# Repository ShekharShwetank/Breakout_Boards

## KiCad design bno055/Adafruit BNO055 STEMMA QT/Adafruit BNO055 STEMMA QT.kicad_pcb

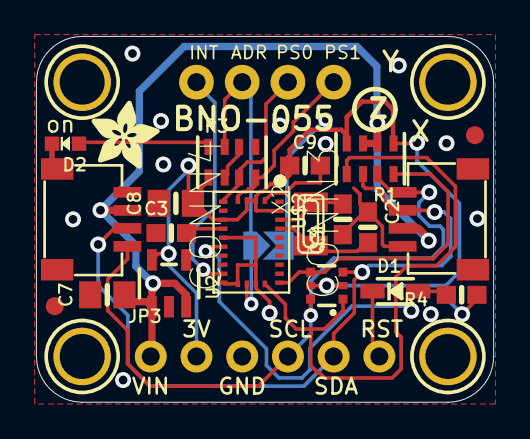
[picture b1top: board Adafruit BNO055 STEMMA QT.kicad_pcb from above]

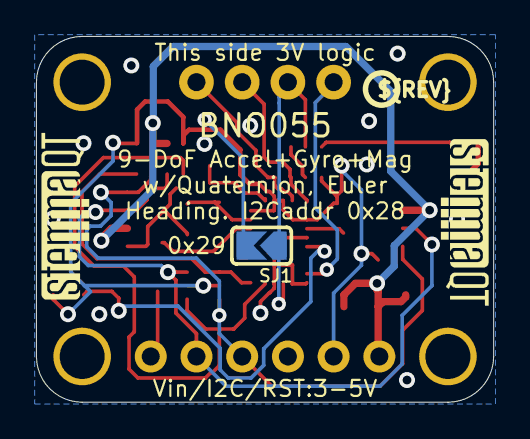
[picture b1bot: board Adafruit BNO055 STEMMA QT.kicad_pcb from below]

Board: 2 copper layers, 25.4 x 20.3 mm, 30 parts (4 on the bottom side), 17 nets.

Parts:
C1, C2: 22pF; 0603-NO
C3, C9: 0.1uF; 0603-NO
C7, C8: 10uF; 0805-NO
CONN3, CONN4: STEMMA_I2C_QT; JST_SH4
D1: 1n4148; SOD-323
D2: GREEN; CHIPLED_0603_NOOUTLINE
FID3, FID4: FIDUCIAL_1MM
JP2: 1X04_ROUND_76
JP3: 1X06_ROUND_70
Q3: BSS138; SOT363
R1, R3: 10K; RESPACK_4X0603
R4: 10K; 0603-NO
SJ1: SOLDERJUMPER_ARROW_NOPASTE
U2: AP2112K-3.3; SOT23-5
U$2: BNO055
U$45, U$46, U$48, U$49: MOUNTINGHOLE2.5; MOUNTINGHOLE_2.5_PLATED
U$51: ADAFRUIT_3.5MM
U$52: PCBFEAT-REV-040
U$53, U$54: STEMMAQT
X2: 32.768; XTAL3215

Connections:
3.3V: C8.1, C9.1, JP3.2, Q3.2, Q3.5, R1.1, R1.4, R3.1, R4.1, SJ1.2, U2.5, U$2.3, U$2.4, U$2.8, U$2.28
GND: C1.1, C2.1, C3.1, C7.2, C8.2, C9.2, CONN3.1, CONN3.MT1, CONN3.MT2, CONN4.1, CONN4.MT1, CONN4.MT2, D2.C, JP3.3, R3.2, R3.5, R3.6, U2.2, U$2.2, U$2.10, U$2.15, U$2.16, U$2.18, U$2.25
I2CADDR_3V: JP2.2, R3.7, SJ1.1, U$2.17
INT_3V: JP2.1, U$2.14
unnamed: C1.2, U$2.27, X2.P$2
unnamed: C2.2, U$2.26, X2.P$1
unnamed: C3.2, U$2.9
unnamed: D2.A, R3.8
NRESET_3V: D1.A, R4.2, U$2.11
PS0_3V: JP2.3, R3.3, U$2.6
PS1_3V: JP2.4, R3.4, U$2.5
RESET: D1.C, JP3.6
SCL: CONN3.4, CONN4.4, JP3.4, Q3.6, R1.7
SCL_3V: Q3.1, R1.5, U$2.19
SDA: CONN3.3, CONN4.3, JP3.5, Q3.3, R1.6
SDA_3V: Q3.4, R1.8, U$2.20
VCC: C7.1, CONN3.2, CONN4.2, JP3.1, R1.2, R1.3, U2.1, U2.3

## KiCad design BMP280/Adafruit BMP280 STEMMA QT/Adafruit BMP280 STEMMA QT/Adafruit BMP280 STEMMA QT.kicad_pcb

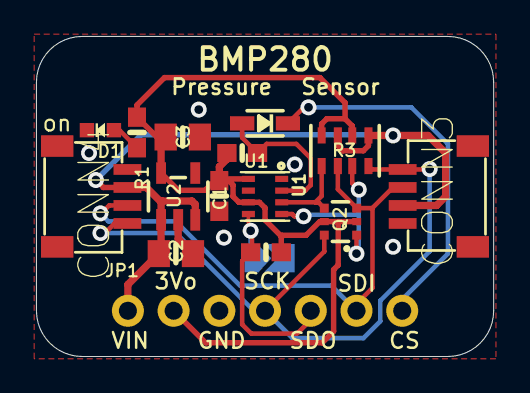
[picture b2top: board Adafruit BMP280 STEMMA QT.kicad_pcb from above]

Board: 2 copper layers, 25.4 x 17.8 mm, 16 parts (1 on the bottom side), 11 nets.

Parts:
C1: 0.1uF; 0603-NO
C2, C3: 10uF; 0805-NO
CONN3, CONN4: STEMMA_I2C_QT; JST_SH4
D1: GREEN; CHIPLED_0603_NOOUTLINE
D2: 1N4148; SOD-323
JP1: HEADER-1X770MIL; 1X07_ROUND_70
Q2: BSS138; SOT363
R1, R4, R5: 10K; 0603-NO
R3: 10K; RESPACK_4X0603
SJ1: SOLDERJUMPER; SOLDERJUMPER_ARROW_NOPASTE
U1: BMP280_COMBO; BMX280_COMBO
U2: AP2112K-3.3; SOT23-5

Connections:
3.3V: C1.1, C3.1, JP1.2, Q2.2 (G), Q2.5 (G), R1.1, R3.2 (1), R3.4 (1), R4.2, R5.2, U1.6 (VDDIO), U1.8 (VDD), U2.5 (OUT)
/CS: D2.C, JP1.7
/CS_3V: D2.A, R5.1, U1.2 (CSB)
/SCK_3V: Q2.1 (S), R3.7 (2), U1.4 (SCK)
/SCK/SCL: CONN3.4 (SCL), CONN4.4 (SCL), JP1.4, Q2.6 (D), R3.8 (2)
/SDI_3V: Q2.4 (S), R3.5 (2), U1.3 (SDI)
/SDI/SDA: CONN3.3 (SDA), CONN4.3 (SDA), JP1.6, Q2.3 (D), R3.6 (2)
/SDO/ADR: JP1.5, R4.1, SJ1.1, U1.5 (SDO)
GND: C1.2, C2.2, C3.2, CONN3.1 (GND), CONN4.1 (GND), D1.C, JP1.3, SJ1.2, U1.1 (GND), U1.7 (GND), U2.2 (GND)
unnamed: D1.A, R1.2
VCC: C2.1, CONN3.2 (V+), CONN4.2 (V+), JP1.1, R3.1, R3.3 (1), U2.1 (IN), U2.3 (EN)

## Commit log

2024-12-20 assets updated
